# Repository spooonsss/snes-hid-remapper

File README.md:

# SNES controller HID Remapper

This is a SNES controller mod for HID Remapper. Basically a SNES Controller->USB gamepad converter. There are two parts: the hardware board that is installed like an arduino shield to the Raspberry Pi Pico, and the modified firmware.

## SNES controller board

snes_rp2040_board/ contains the KiCAD project for the board. Components are available from the usual suppliers, except the SNES controller socket can be found on Amazon/EBay/AliExpress. Alternatively, you use a cut extension cable. Don't forget to buy the DIP headers if your Pico did not come with any. Note that some Picos (like the ones I bought from AliExpress) come with a micro-USB connector instead of a USB C, so choose according to your preference.

BOM:  
J1 snes_controller_socket  
C1,C2,C3 0603 0.1uF  
IC1,IC2,IC3 SN74LV1T34DBVR  
J2 PICO+headers  
R1 0603 100k  

Do not populate J3, IC4, or R2.

I've used OSHPark to manufacture the board. OSHPark will take a KiCAD PCB file directly. Note the SNES board SMT components face the PICO, and the front side of the PICO (with the CPU, LED and button) faces away from the SNES board. The easiest order of soldering: SNES board SMT components, SNES board DIP headers, SNES board controller socket, then PICO DIP headers.

After the board is manufactured, flash the firmware by holding down the BOOTSEL button while plugging in the USB and copying `remapper_snes.uf2` to `D:\` (or whatever drive letter was chosen). Then use Chrome: https://www.jfedor.org/hid-remapper-config/v14 Open device. Actions> Import JSON> `snes-hid-remapper-config.json` to load the example configuration.

https://gamepadviewer.com/ is useful for showing the inputs received.

To compile: add `#include <cstdint>`  to `firmware/pico-sdk/tools/pioasm/pio_disassembler.h`

Performance: the SNES controller is read about 4200 times per second to minimize input delay. I don't have a measurement for end-to-end delay.

# Original README follows:

# HID Remapper

This is a configurable USB dongle that allows you to remap inputs from mice, keyboards and other devices. It works completely in hardware and requires no software running on the computer during normal use.

It can do things like reassign buttons, change keyboard layouts, map mouse buttons to keyboard inputs, map keystrokes to mouse inputs, change mouse sensitivity (permanently or when a button is held), rotate mouse axes by arbitrary (non-90 degree) angles, drag-lock for mouse buttons, scroll by moving the mouse, and much more.

It is configurable [through a web browser](https://www.jfedor.org/hid-remapper-config/) using WebHID (Chrome or Chrome-based browser required).

Wireless receivers are supported and multiple devices can be connected at the same time using a USB hub (with different mappings for each device if desired).

In addition to the remapping functionality, it can do polling rate overclocking up to 1000 Hz.

A separate [serial](SERIAL.md) version of the remapper takes inputs from a serial (RS-232) mouse and translates them to USB.

There's also a [Bluetooth](BLUETOOTH.md) version that runs on nRF52840-based boards, which translates Bluetooth inputs to USB.

## How to make the device

There are three main ways of making the HID Remapper. You can either buy [this board](https://www.adafruit.com/product/5723) from Adafruit, make it yourself using a Raspberry Pi Pico (or two), or you can use the provided files to manufacture a custom board at JLCPCB or a similar service. The functionality is the same in all cases.

If you get the Feather RP2040 USB Host board from Adafruit, the device is ready to use, you just need to flash it with the right firmware ([remapper\_feather.uf2](https://github.com/jfedor2/hid-remapper/releases/latest/download/remapper_feather.uf2)). Hold the "Boot" button on the board, then press the "Reset" button. A USB drive should show up on your computer. Copy the UF2 file to that drive. That's it.

See [here](HARDWARE.md) for details on how to make the Pico variants of the device and [here](custom-boards/) for details on the custom board option.

## How to use the configuration tool

A live version of the web configuration tool can be found [here](https://www.jfedor.org/hid-remapper-config/). It only works in Chrome and Chrome-based browsers (including ChromeOS). On Linux you might need to give yourself permissions to the appropriate `/dev/hidraw*` device.

The input remapping mechanism is based on a list of _mappings_. Every mapping has an input and an output. Inputs and outputs are things like mouse buttons, mouse axes, keyboard keys etc. For example if you want the right mouse button to act as the left mouse button, add a mapping with input set to "Right button" and output set to "Left button".

By default all inputs that aren't explicitly mapped to anything are passed through unchanged. If you don't want that, you can uncheck the "Unmapped inputs passthrough" checkbox (for each layer separately, see below).

There can be more than one mapping with the same input and the same output. It is useful when you want to map a mouse button to, say, Ctrl-C. You can achieve that by adding two mappings, both with that button as input, one with "Control" as output and one with "C" as output.

Similarly to remapping buttons, you can also remap axes. For example if you want horizontal mouse movements to be mapped to vertical cursor movements on the computer, add a mapping with the input set to "Cursor X" and the output set to "Cursor Y".

If you want to change cursor speed (mouse sensitivity), you can use the _scaling_ part of the mapping. By default it is set to 1, but you could add mappings with the same axes for inputs and outputs and for example set scaling to 2 to make the cursor move twice as fast, or set it to -1 to invert the direction of the movement. (Usually it's best to first increase the CPI on the device if possible as that will give you better precision.)

You can have a mapping that has a button or a key as input and an axis as output. For example if you add a mapping with "Right arrow" as input and "Cursor X" as output, it will make the cursor move right when right arrow is held on the keyboard.

Having an axis as input and a button as output currently doesn't make a lot of sense.

The _sticky_ flag on a mapping can be used to implement drag-lock functionality. When the flag is enabled on a mapping, pressing (and releasing) the input button will cause the output button to be held until the input button is pressed again.

The _layers_ mechanism might sound familiar if you ever used a custom ergo keyboard. It works as follows. A special mapping can be added with some button as input and "Layer X" as output. This means that when that button is pressed, layer X is active and therefore mappings from layer X are applied. Every mapping has a set of layers on which it is present. If no layer is explicitly activated, layer 0 is active. More than one layer can be active at the same time. This mechanism has many useful applications, from completely separate keyboard layouts to things like "sniper button" on a mouse - increasing precision when a certain button is held.

Layer activating mappings can be sticky.

_Tap-hold_ is another mechanism adopted from the custom ergo keyboard world. It lets you map the same button to different things depending on whether it's _tapped_ (pressed and released quickly) or _held_ (longer than 200ms or whatever you set the threshold to). This allows configurations where a button keeps its primary function when it's clicked, but activates a layer (or a modifier key like Shift) when it's held. Together with the sticky flag, it can also be used to make a button activate a layer permanently when clicked and also temporarily when held. For the last configuration to work properly, create two separate mappings, one with "sticky"+"tap" enabled, and another with "hold" enabled.

Sometimes you want a certain button to send multiple outputs, but not at the same time, but one after another, for example to input a special character by typing something like Alt-0165 or to emulate a double click. You can do that with the _macros_ feature. Each macro is defined as a list of inputs that will be sent one after another. Every input can consist of multiple keys, for example you can have a macro that looks like this: `Left Shift+H, E, L, Nothing, L, O` that will type the string "Hello" or you can have a macro that looks like this: `Left Alt+Numpad 0, Left Alt+Numpad 1, Left Alt+Numpad 6, Left Alt+Numpad 5` that will enter the yen symbol (on some systems). Or, to emulate a double-click, you could define a macro that looks like this: `Left button, Nothing, Left button`. The "Nothing" part is necessary for the computer to register a "button-up" event, otherwise the first macro would type "Helo" and the last one would just work as a single click.

To make a button send a certain macro, add a mapping with that button as input and with "Macro X" as output.

The _expressions_ mechanism is an advanced and experimental feature that can be used for more complex mappings. Among other things it lets you map things like analog sticks, triggers and D-pads on game controllers, applying dead zones and other non-linear transformations to them. See [here](EXPRESSIONS.md) for more info on how to use them.

The configuration tool comes with a list of standard inputs like mouse buttons and axes, keyboard keys and media keys like play/pause, mute, etc. Some devices will use inputs from outside that list. Good news is they can still be mapped. To make the device-specific inputs appear on the list, just connect your device to the remapper, and the remapper to your computer, and click the "Open device" button before you define the mappings. The configuration tool will fetch the list of inputs declared by your device and they will show up at the bottom of the input list. Unfortunately they will only appear as hex codes and will not have human friendly names. Therefore it might require some trial and error to find the input you want (and some devices will have a lot of them!).

The remapper supports high-resolution mouse scrolling on the output side, which should work on Windows and modern Linux desktops. To experience it, add a mapping with "Cursor Y" as input and "V scroll" as output (perhaps on a layer). The "Partial scroll timeout" setting is related to this and you can safely ignore it if you're not mapping anything to mouse scroll. It applies when high-resolution scrolling is _not_ in use and is the time after which a "half-tick" of the scroll is forgotten.

If you set the "Polling rate override" to anything else than "don't override", it will use the selected polling rate instead of the polling rate requested by the connected device. Keep in mind this doesn't work for all devices.

If you're getting an "Incompatible version" error, try upgrading to the newest firmware.

If this description wasn't particularly clear for you, perhaps looking at some of the examples that come with the configuration tool will help.

If you can't use the browser-based configuration tool, there's also a [command-line tool](config-tool) that takes JSON in the same format as the web tool on standard input. I only tested it on Linux, but in theory it should also run on Windows and Mac.

## How to update the firmware

The procedure to update the firmware is similar on all variants. When you go to the configuration website and try to connect to your device when it doesn't have the latest firmware, you will get a message and a link to a version of the configuration interface that is compatible with your current (old) firmware. Click that link, connect to your HID Remapper by clicking "Open device" as usual, then go to the "Actions" tab and click "Flash firmware". This will put your device in firmware flashing mode. A drive should appear on your computer. For all the RP2040-based variants, the drive will be named "RPI-RP2". For the Bluetooth variants, it will be called something else, depending on what board you're using. Download the correct firmware file for your variant (see table below) and copy it to that drive. If the table below says "no" in the "Flash B side required" column then you're done. Go back to the regular version of the configuration interface and carry on. If it says "yes" in that column then before continuing you need to also flash the B side. Connect to your HID Remapper (using the regular version of the configuration interface), then go to the "Actions" tab and click "Flash B side". Then disconnect and reconnect your HID Remapper and you're done.

If you're using the dual Pico variant then you need to flash the A side using the [remapper\_dual\_a.uf2](https://github.com/jfedor2/hid-remapper/releases/latest/download/remapper_dual_a.uf2) file as described above and then flash the B side manually. Disconnect your HID Remapper from your computer, disconnect the OTG adapter from the B-side Pico, hold the BOOTSEL button on the B-side Pico and then, while holding the button, connect the B-side Pico to your computer. A drive named "RPI-RP2" should appear. Copy the [remapper\_dual\_b.uf2](https://github.com/jfedor2/hid-remapper/releases/latest/download/remapper_dual_b.uf2) file to that drive. Disconnect the B-side Pico from your computer, reconnect the OTG adapter and reconnect your HID Remapper to your computer.

When updating firmware, the current configuration on your HID Remapper is preserved. For extra peace of mind you can export your configuration to a JSON file before performing the update. That way if you need to revert to the old version of the firmware for any reason, you'll be able to import the configuration from the JSON file (configuration is lost when going from a newer firmware to an older firmware).

variant | firmware file(s) | "Flash B side" required
------- | ---------------- | -----------------------
single Pico | [remapper.uf2](https://github.com/jfedor2/hid-remapper/releases/latest/download/remapper.uf2) | no
dual Pico | [remapper\_dual\_a.uf2](https://github.com/jfedor2/hid-remapper/releases/latest/download/remapper_dual_a.uf2)<br>[remapper\_dual\_b.uf2](https://github.com/jfedor2/hid-remapper/releases/latest/download/remapper_dual_b.uf2) | flash B side manually
Feather RP2040 with USB Host | [remapper\_feather.uf2](https://github.com/jfedor2/hid-remapper/releases/latest/download/remapper_feather.uf2) | no
Waveshare RP2040-PiZero | [remapper\_waveshare\_rp2040\_pizero.uf2](https://github.com/jfedor2/hid-remapper/releases/latest/download/remapper_waveshare_rp2040_pizero.uf2) | no
custom board v1 | [remapper\_board.uf2](https://github.com/jfedor2/hid-remapper/releases/latest/download/remapper_board.uf2) | yes
custom board v2 | [remapper\_board.uf2](https://github.com/jfedor2/hid-remapper/releases/latest/download/remapper_board.uf2) | yes
custom board v3 | [remapper\_feather.uf2](https://github.com/jfedor2/hid-remapper/releases/latest/download/remapper_feather.uf2) | no
custom board v4 | [remapper\_feather.uf2](https://github.com/jfedor2/hid-remapper/releases/latest/download/remapper_feather.uf2) | no
custom board v5 | [remapper\_board.uf2](https://github.com/jfedor2/hid-remapper/releases/latest/download/remapper_board.uf2) | yes
custom board v6 | [remapper\_board.uf2](https://github.com/jfedor2/hid-remapper/releases/latest/download/remapper_board.uf2) | yes
custom board v7 | [remapper\_board\_v7.uf2](https://github.com/jfedor2/hid-remapper/releases/latest/download/remapper_board_v7.uf2) | yes
custom board v8 | [remapper\_board\_v8.uf2](https://github.com/jfedor2/hid-remapper/releases/latest/download/remapper_board_v8.uf2) | no
Feather nRF52840 Express | [remapper_adafruit_feather_nrf52840.uf2](https://github.com/jfedor2/hid-remapper/releases/latest/download/remapper_adafruit_feather_nrf52840.uf2) | no
Xiao nRF52840 | [remapper_seeed_xiao_nrf52840.uf2](https://github.com/jfedor2/hid-remapper/releases/latest/download/remapper_seeed_xiao_nrf52840.uf2) | no
serial | [remapper_serial.uf2](https://github.com/jfedor2/hid-remapper/releases/latest/download/remapper_serial.uf2) | no

## How to compile the firmware

The easiest way to compile the firmware is to let GitHub do it for you. This repository has GitHub Actions that build the firmware, so you can just fork, make your changes, wait for the job to complete, and look for the binaries in the artifacts produced.

To compile the RP2040 firmware on your machine, use the following steps (details may vary depending on your Linux distribution):

```
sudo apt install gcc-arm-none-eabi libnewlib-arm-none-eabi libstdc++-arm-none-eabi-newlib srecord
git clone https://github.com/jfedor2/hid-remapper.git
cd hid-remapper
git submodule update --init
cd firmware
mkdir build
cd build
cmake ..
# or, to build for the custom boards:
# PICO_BOARD=remapper cmake ..
make
```

To compile the nRF52 firmware, you can either follow [Nordic's setup instructions](https://docs.nordicsemi.com/bundle/ncs-latest/page/nrf/installation.html) and then `west build -b seeed_xiao_nrf52840` to compile the firmware, or you can use Docker with a command like this (start from the top level of the repository or adjust the path accordingly):

```
docker run --rm -v $(pwd):/workdir/project -w /workdir/project/firmware-bluetooth nordicplayground/nrfconnect-sdk:v2.2-branch west build -b seeed_xiao_nrf52840
```

## License

The software in this repository is licensed under the [MIT License](LICENSE), unless stated otherwise.

The hardware designs in this repository are licensed under the Creative Commons Attribution 4.0 International license ([CC BY 4.0](https://creativecommons.org/licenses/by/4.0/)), unless stated otherwise.

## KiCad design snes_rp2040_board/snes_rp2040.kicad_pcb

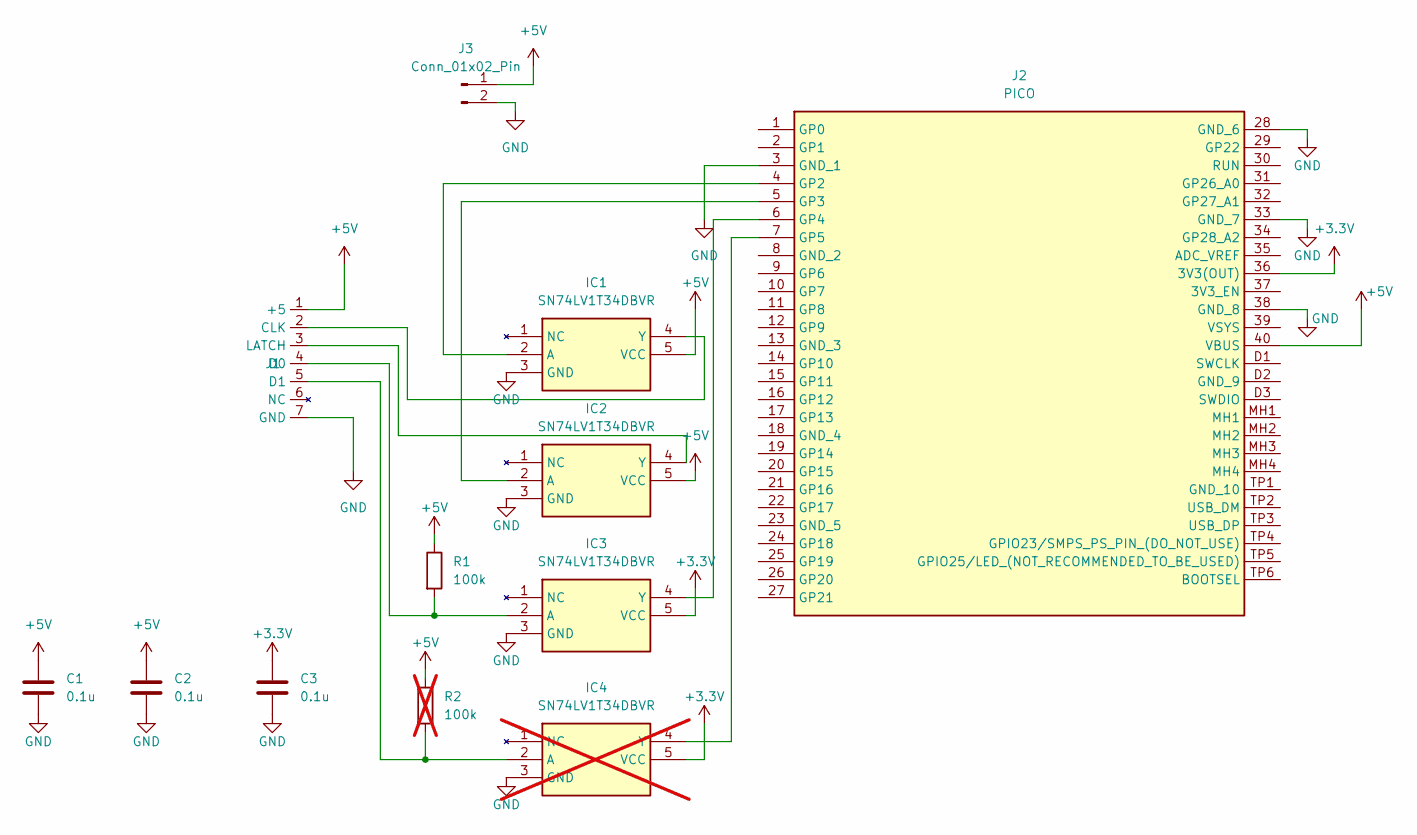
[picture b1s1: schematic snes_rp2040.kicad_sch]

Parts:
C1, C2, C3: 0.1u; C_0603_1608Metric_Pad1.08x0.95mm_HandSolder
IC1, IC2, IC3: SN74LV1T34DBVR; SOT95P280X145-5N; Manufacturer_Part_Number SN74LV1T34DBVR; Mouser Part Number 595-SN74LV1T34DBVR
IC4: SN74LV1T34DBVR; SOT95P280X145-5N; Manufacturer_Part_Number SN74LV1T34DBVR; Mouser Part Number 595-SN74LV1T34DBVR; not fitted
J1: snes_controller_socket
J2: PICO; PICO_DIP_40_no16-26; Manufacturer_Part_Number PICO
J3: Conn_01x02_Pin; PinHeader_1x02_P2.54mm_Vertical
R1: 100k; R_0603_1608Metric_Pad0.98x0.95mm_HandSolder
R2: 100k; R_0603_1608Metric_Pad0.98x0.95mm_HandSolder; not fitted

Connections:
+3.3V: C3.1, IC3.5 (VCC), IC4.5 (VCC), J2.36 (3V3(OUT))
+5V: C1.1, C2.1, IC1.5 (VCC), IC2.5 (VCC), J1.1 (+5), J2.40 (VBUS), J3.1, R1.1, R2.1
GND: C1.2, C2.2, C3.2, IC1.3 (GND), IC2.3 (GND), IC3.3 (GND), IC4.3 (GND), J1.7 (GND), J2.3 (GND_1), J2.28 (GND_6), J2.33 (GND_7), J2.38 (GND_8), J3.2
unnamed: IC1.2 (A), J2.4 (GP2)
unnamed: IC1.4 (Y), J1.2 (CLK)
unnamed: IC2.2 (A), J2.5 (GP3)
unnamed: IC2.4 (Y), J1.3 (LATCH)
unnamed: IC3.2 (A), J1.4 (D0), R1.2
unnamed: IC3.4 (Y), J2.6 (GP4)
unnamed: IC4.2 (A), J1.5 (D1), R2.2
unnamed: IC4.4 (Y), J2.7 (GP5)

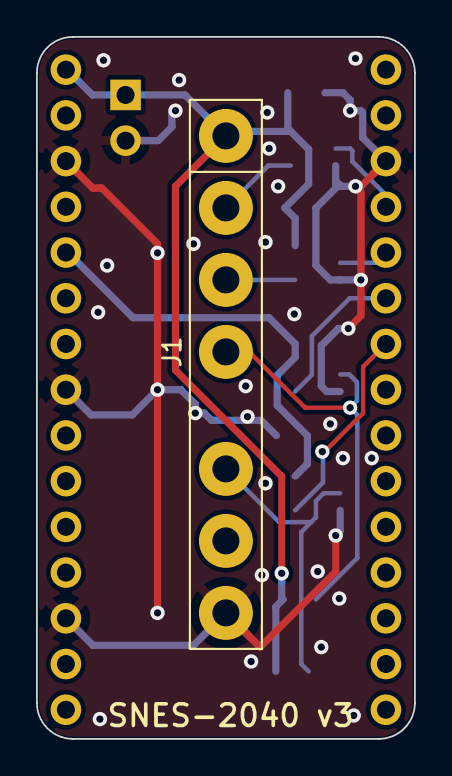
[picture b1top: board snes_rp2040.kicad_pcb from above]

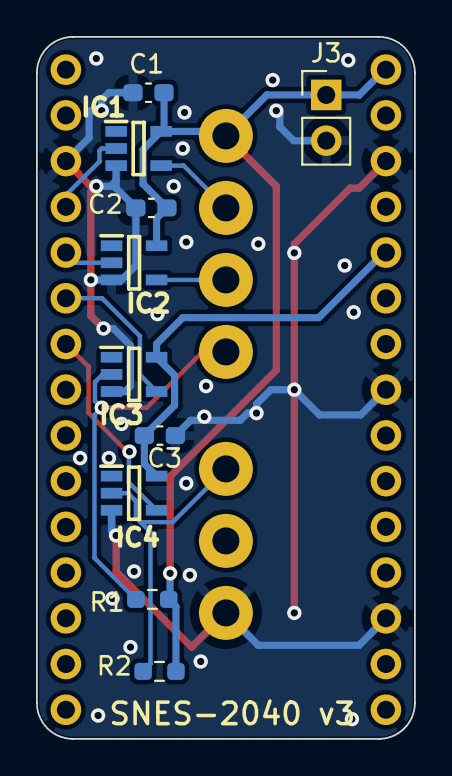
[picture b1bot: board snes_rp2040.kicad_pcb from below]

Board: 2 copper layers, 21.0 x 39.0 mm, 12 parts (11 on the bottom side), 11 nets.

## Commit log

2024-10-20 Fake snes input
2024-11-13 snes board v3
